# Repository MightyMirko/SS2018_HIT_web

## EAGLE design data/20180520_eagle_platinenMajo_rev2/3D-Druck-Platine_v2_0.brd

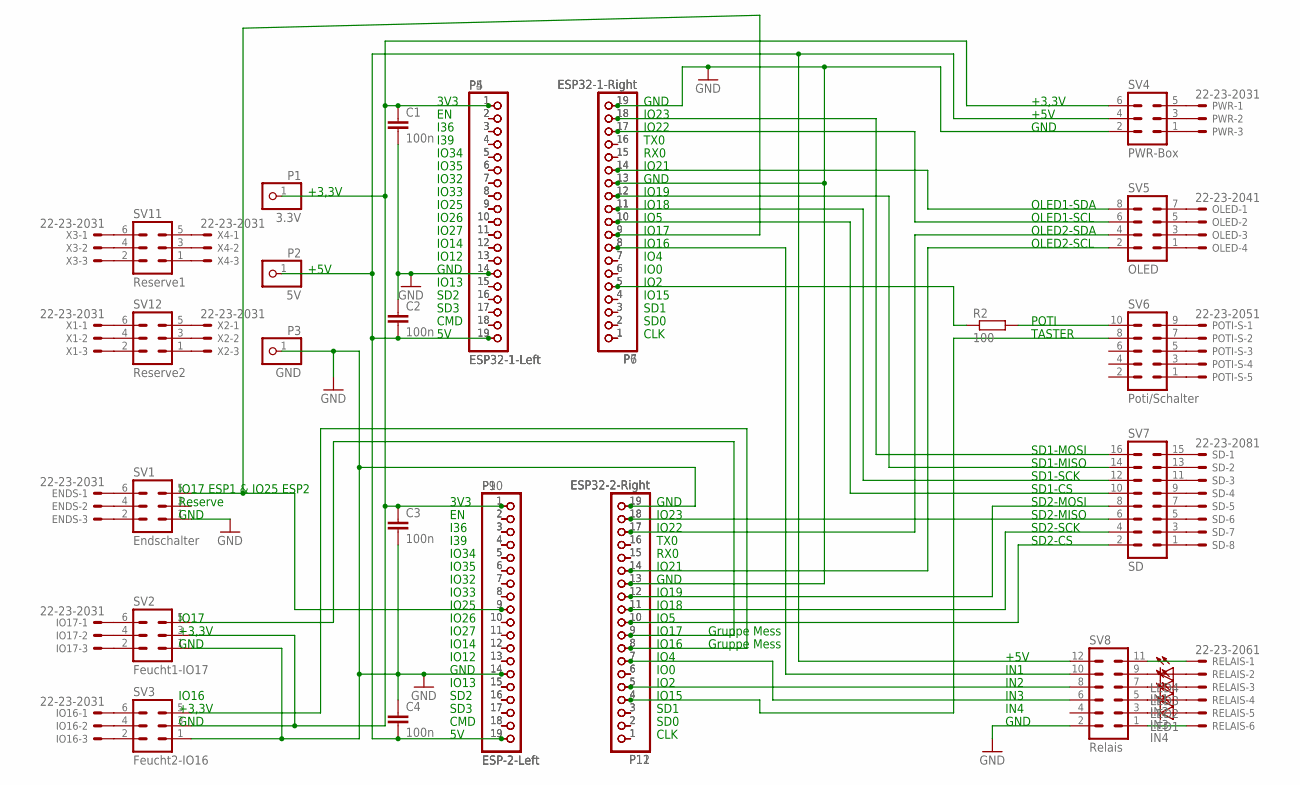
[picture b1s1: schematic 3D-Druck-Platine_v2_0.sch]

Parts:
C1, C2, C3, C4: 100n; C025-024X044
ENDS: 22-23-2031
IO16, IO17: 22-23-2031
LED1: IN4; LED3MM
LED2: IN3; LED3MM
LED3: IN2; LED3MM
LED4: IN1; LED3MM
OLED: 22-23-2041
P1: 3.3V; 1X01
P2: 5V; 1X01
P3: GND; 1X01
P4, P5: ESP32-1-Left; 1X19
P6, P7: ESP32-1-Right; 1X19
P9, P10: ESP-2-Left; 1X19
P11, P12: ESP32-2-Right; 1X19
POTI-S: 22-23-2051
PWR: 22-23-2031
R2: 100; 0207/10
RELAIS: 22-23-2061
SD: 22-23-2081
SV1: Endschalter; MA03-2
SV2: Feucht1-IO17; MA03-2
SV3: Feucht2-IO16; MA03-2
SV4: PWR-Box; MA03-2
SV5: OLED; MA04-2
SV6: Poti/Schalter; MA05-2
SV7: SD; MA08-2
SV8: Relais; MA06-2
SV11: Reserve1; MA03-2
SV12: Reserve2; MA03-2
X1, X2, X3, X4: 22-23-2031

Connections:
GND: C1.2, C2.1, C3.2, C4.1, P3.1, P4.14, P5.14, P6.13, P6.19, P7.13, P7.19, P9.14, P10.14, P11.13, P11.19, P12.13, P12.19, SV1.1, SV2.1, SV3.1, SV4.2, SV8.2
unnamed: P4.2, P5.2
unnamed: LED4.K (C), SV8.9
unnamed: P4.3, P5.3
unnamed: C1.1, C3.1, P1.1, P4.1, P5.1, P9.1, P10.1, SV2.3, SV3.3, SV4.6
unnamed: P11.8, P12.8, SV3.5
unnamed: LED3.K (C), SV8.7
unnamed: C2.2, C4.2, P2.1, P4.19, P5.19, P9.19, P10.19, SV4.4, SV8.12
unnamed: P4.4, P5.4
unnamed: P4.5, P5.5
unnamed: ENDS.1, SV1.6
unnamed: P4.6, P5.6
unnamed: IO17.1, SV2.6
unnamed: ENDS.2, SV1.4
unnamed: ENDS.3, SV1.2
unnamed: IO17.2, SV2.4
unnamed: IO17.3, SV2.2
unnamed: IO16.1, SV3.6
unnamed: IO16.2, SV3.4
unnamed: IO16.3, SV3.2
unnamed: PWR.1, SV4.5
unnamed: PWR.2, SV4.3
unnamed: LED2.K (C), SV8.5
unnamed: P4.7, P5.7
unnamed: P4.8, P5.8
unnamed: P4.9, P5.9
unnamed: P4.10, P5.10
unnamed: P4.11, P5.11
unnamed: P4.12, P5.12
unnamed: P4.13, P5.13
unnamed: P4.15, P5.15
unnamed: P4.16, P5.16
unnamed: P4.17, P5.17
unnamed: P4.18, P5.18
unnamed: P6.1, P7.1
unnamed: P6.2, P7.2
unnamed: P6.3, P7.3
unnamed: P6.4, P7.4
unnamed: PWR.3, SV4.1
unnamed: P6.7, P7.7
unnamed: P6.15, P7.15
unnamed: P6.16, P7.16
unnamed: P9.2, P10.2
unnamed: P9.3, P10.3
unnamed: P9.4, P10.4
unnamed: P9.5, P10.5
unnamed: P9.6, P10.6
unnamed: P9.8, P10.8
unnamed: P9.11, P10.11
unnamed: P9.12, P10.12
unnamed: P9.13, P10.13
unnamed: P9.15, P10.15
unnamed: P9.16, P10.16
unnamed: P9.17, P10.17
unnamed: P9.18, P10.18
unnamed: P11.1, P12.1
unnamed: P11.2, P12.2
unnamed: P11.3, P12.3
unnamed: OLED.1, SV5.7
unnamed: P11.6, P12.6
unnamed: P11.15, P12.15
unnamed: R2.2, SV6.10
unnamed: P6.6, P7.6
unnamed: OLED.2, SV5.5
unnamed: OLED.3, SV5.3
unnamed: OLED.4, SV5.1
unnamed: POTI-S.1, SV6.9
unnamed: POTI-S.2, SV6.7
unnamed: POTI-S.3, SV6.5
unnamed: POTI-S.4, SV6.3
unnamed: POTI-S.5, SV6.1
unnamed: SD.1, SV7.15
unnamed: SD.2, SV7.13
unnamed: SD.3, SV7.11
unnamed: SD.5, SV7.7
unnamed: SD.6, SV7.5
unnamed: SD.7, SV7.3
unnamed: SD.8, SV7.1
unnamed: SD.4, SV7.9
unnamed: RELAIS.1, SV8.11
unnamed: LED1.K (C), SV8.3
unnamed: LED4.A, RELAIS.2
unnamed: LED3.A, RELAIS.3
unnamed: LED2.A, RELAIS.4
unnamed: RELAIS.6, SV8.1
unnamed: LED1.A, RELAIS.5
unnamed: SV11.6, X3.1
unnamed: SV11.4, X3.2
unnamed: SV11.2, X3.3
unnamed: SV11.5, X4.1
unnamed: SV11.3, X4.2
unnamed: SV11.1, X4.3
unnamed: SV12.6, X1.1
unnamed: SV12.4, X1.2
unnamed: SV12.2, X1.3
unnamed: SV12.5, X2.1
unnamed: SV12.3, X2.2
unnamed: SV12.1, X2.3
unnamed: P11.16, P12.16
N$ESP1-18: P6.11, P7.11, SV7.12
N$ESP1-IO2: P6.5, P7.5, R2.1
N$ESP1-IO5: P6.10, P7.10, SV7.10
N$ESP1-IO16: P6.8, P7.8, SV8.10
N$ESP1-IO17_ESP2-IO25: P6.9, P7.9, P9.9, P10.9, SV1.5
N$ESP1-IO19: P6.12, P7.12, SV7.14
N$ESP1-IO21: P6.14, P7.14, SV5.8
N$ESP1-IO22: P6.17, P7.17, SV5.6
N$ESP1-IO23: P6.18, P7.18, SV7.16
N$ESP2-IO2: P11.5, P12.5, SV8.8
N$ESP2-IO4: P11.7, P12.7, SV8.6
N$ESP2-IO5: P11.10, P12.10, SV7.2
N$ESP2-IO15: P11.4, P12.4, SV6.8
N$ESP2-IO16: P11.9, P12.9, SV2.5
N$ESP2-IO18: P11.11, P12.11, SV7.4
N$ESP2-IO19: P11.12, P12.12, SV7.8
N$ESP2-IO21: P11.14, P12.14, SV5.2
N$ESP2-IO22: P11.17, P12.17, SV5.4
N$ESP2-IO23: P11.18, P12.18, SV7.6
N$ESP2-IO26: P9.10, P10.10
N$ESP2-IO32: P9.7, P10.7

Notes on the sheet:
3V3
I36
I39
IO34
IO35
IO32
IO33
IO25
IO26
IO27
IO14
IO12
GND
IO13
SD2
SD3
CMD
IO23
IO22
TX0
RX0
IO21
IO18
IO19
IO5
IO17
IO16
IO4
IO0
IO2
IO15
SD1
SD0
CLK
+5V
+3,3V
OLED1-SDA
OLED2-SDA
OLED2-SCL
OLED1-SCL

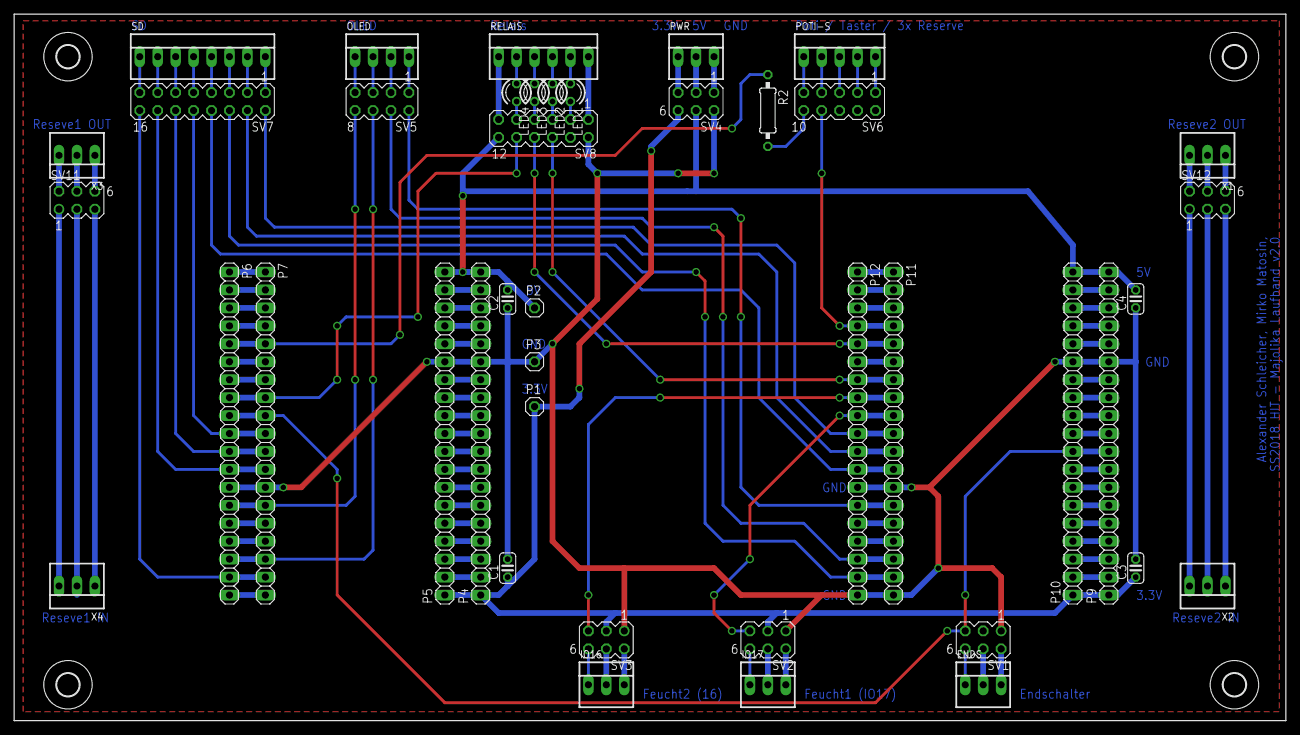
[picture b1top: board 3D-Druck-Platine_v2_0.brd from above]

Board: 2 copper layers, 180.0 x 100.0 mm, 46 parts (0 on the bottom side), 120 nets.

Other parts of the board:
U$1, U$2, U$3, U$4: 3,2

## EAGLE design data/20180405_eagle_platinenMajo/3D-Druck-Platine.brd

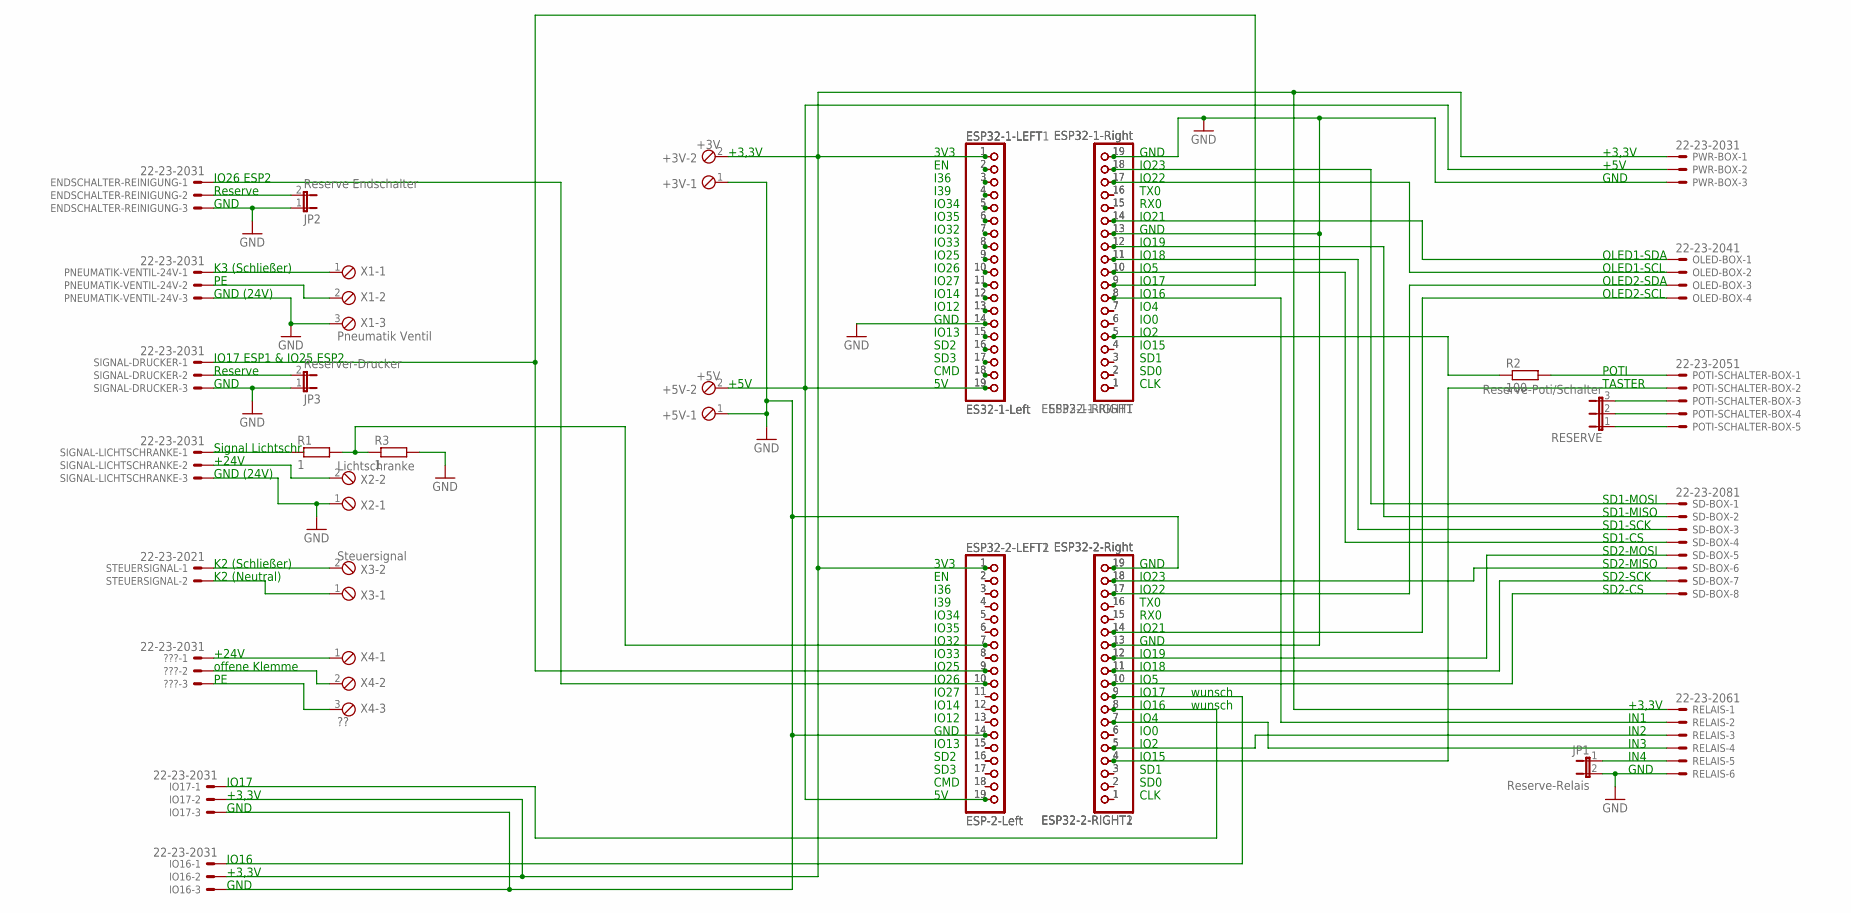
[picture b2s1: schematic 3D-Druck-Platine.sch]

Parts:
+3V: +3V; 2POL254
+5V: +5V; 2POL254
???: 22-23-2031
ENDSCHALTER-REINIGUNG: 22-23-2031
ESP32-1-LEFT, ESP32-1-LEFT1: ES32-1-Left; 1X19
ESP32-1-RIGHT, ESP32-1-RIGHT1: ESP32-1-Right; 1X19
ESP32-2-LEFT1, ESP32-2-LEFT2: ESP-2-Left; 1X19
ESP32-2-RIGHT1, ESP32-2-RIGHT2: ESP32-2-Right; 1X19
IO16, IO17: 22-23-2031
JP1: Reserve-Relais; JP1
JP2: Reserve Endschalter; JP1
JP3: Reserver-Drucker; JP1
OLED-BOX: 22-23-2041
PNEUMATIK-VENTIL-24V: 22-23-2031
POTI-SCHALTER-BOX: 22-23-2051
PWR-BOX: 22-23-2031
R1, R3: 1; 0207/10
R2: 100; 0207/10
RELAIS: 22-23-2061
RESERVE: Reserve-Poti/Schalter; JP2
SD-BOX: 22-23-2081
SIGNAL-DRUCKER: 22-23-2031
SIGNAL-LICHTSCHRANKE: 22-23-2031
STEUERSIGNAL: 22-23-2021
X1: Pneumatik Ventil; 3POL254
X2: Lichtschranke; 2POL254
X3: Steuersignal; 2POL254
X4: ??; 3POL254

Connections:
GND: +3V.1, +5V.1, ENDSCHALTER-REINIGUNG.3, ESP32-1-LEFT.14, ESP32-1-LEFT1.14, ESP32-1-RIGHT.13, ESP32-1-RIGHT.19, ESP32-1-RIGHT1.13, ESP32-1-RIGHT1.19, ESP32-2-LEFT1.14, ESP32-2-LEFT2.14, ESP32-2-RIGHT1.13, ESP32-2-RIGHT1.19, ESP32-2-RIGHT2.13, ESP32-2-RIGHT2.19, IO16.3, IO17.3, JP1.2, JP2.1, JP3.1, PNEUMATIK-VENTIL-24V.3, PWR-BOX.3, R3.2, RELAIS.6, SIGNAL-DRUCKER.3, SIGNAL-LICHTSCHRANKE.3, X1.3, X2.1
unnamed: ESP32-1-LEFT.2, ESP32-1-LEFT1.2
unnamed: POTI-SCHALTER-BOX.3, RESERVE.3
unnamed: ESP32-1-LEFT.3, ESP32-1-LEFT1.3
unnamed: +3V.2, ESP32-1-LEFT.1, ESP32-1-LEFT1.1, ESP32-2-LEFT1.1, ESP32-2-LEFT2.1, IO16.2, IO17.2, PWR-BOX.1, RELAIS.1
unnamed: POTI-SCHALTER-BOX.4, RESERVE.2
unnamed: POTI-SCHALTER-BOX.5, RESERVE.1
unnamed: +5V.2, ESP32-1-LEFT.19, ESP32-1-LEFT1.19, ESP32-2-LEFT1.19, ESP32-2-LEFT2.19, PWR-BOX.2
unnamed: ESP32-1-LEFT.4, ESP32-1-LEFT1.4
unnamed: ESP32-1-LEFT.5, ESP32-1-LEFT1.5
unnamed: ENDSCHALTER-REINIGUNG.2, JP2.2
unnamed: ESP32-1-LEFT.6, ESP32-1-LEFT1.6
unnamed: JP3.2, SIGNAL-DRUCKER.2
unnamed: R1.1, SIGNAL-LICHTSCHRANKE.1
unnamed: SIGNAL-LICHTSCHRANKE.2, X2.2
unnamed: PNEUMATIK-VENTIL-24V.1, X1.1
unnamed: STEUERSIGNAL.1, X3.2
unnamed: STEUERSIGNAL.2, X3.1
unnamed: PNEUMATIK-VENTIL-24V.2, X1.2
unnamed: ???.1, X4.1
unnamed: ???.2, X4.2
unnamed: ???.3, X4.3
unnamed: JP1.1, RELAIS.5
unnamed: ESP32-1-LEFT.7, ESP32-1-LEFT1.7
unnamed: ESP32-1-LEFT.8, ESP32-1-LEFT1.8
unnamed: ESP32-1-LEFT.9, ESP32-1-LEFT1.9
unnamed: ESP32-1-LEFT.10, ESP32-1-LEFT1.10
unnamed: ESP32-1-LEFT.11, ESP32-1-LEFT1.11
unnamed: ESP32-1-LEFT.12, ESP32-1-LEFT1.12
unnamed: ESP32-1-LEFT.13, ESP32-1-LEFT1.13
unnamed: ESP32-1-LEFT.15, ESP32-1-LEFT1.15
unnamed: ESP32-1-LEFT.16, ESP32-1-LEFT1.16
unnamed: ESP32-1-LEFT.17, ESP32-1-LEFT1.17
unnamed: ESP32-1-LEFT.18, ESP32-1-LEFT1.18
unnamed: ESP32-1-RIGHT.1, ESP32-1-RIGHT1.1
unnamed: ESP32-1-RIGHT.2, ESP32-1-RIGHT1.2
unnamed: ESP32-1-RIGHT.3, ESP32-1-RIGHT1.3
unnamed: ESP32-1-RIGHT.4, ESP32-1-RIGHT1.4
unnamed: ESP32-1-RIGHT.7, ESP32-1-RIGHT1.7
unnamed: ESP32-1-RIGHT.15, ESP32-1-RIGHT1.15
unnamed: ESP32-1-RIGHT.16, ESP32-1-RIGHT1.16
unnamed: ESP32-2-LEFT1.2, ESP32-2-LEFT2.2
unnamed: ESP32-2-LEFT1.3, ESP32-2-LEFT2.3
unnamed: ESP32-2-LEFT1.4, ESP32-2-LEFT2.4
unnamed: ESP32-2-LEFT1.5, ESP32-2-LEFT2.5
unnamed: ESP32-2-LEFT1.6, ESP32-2-LEFT2.6
unnamed: ESP32-2-LEFT1.8, ESP32-2-LEFT2.8
unnamed: ESP32-2-LEFT1.11, ESP32-2-LEFT2.11
unnamed: ESP32-2-LEFT1.12, ESP32-2-LEFT2.12
unnamed: ESP32-2-LEFT1.13, ESP32-2-LEFT2.13
unnamed: ESP32-2-LEFT1.15, ESP32-2-LEFT2.15
unnamed: ESP32-2-LEFT1.16, ESP32-2-LEFT2.16
unnamed: ESP32-2-LEFT1.17, ESP32-2-LEFT2.17
unnamed: ESP32-2-LEFT1.18, ESP32-2-LEFT2.18
unnamed: ESP32-2-RIGHT1.1, ESP32-2-RIGHT2.1
unnamed: ESP32-2-RIGHT1.2, ESP32-2-RIGHT2.2
unnamed: ESP32-2-RIGHT1.3, ESP32-2-RIGHT2.3
unnamed: ESP32-2-RIGHT1.6, ESP32-2-RIGHT2.6
unnamed: ESP32-2-RIGHT1.15, ESP32-2-RIGHT2.15
unnamed: POTI-SCHALTER-BOX.1, R2.2
unnamed: ESP32-1-RIGHT.6, ESP32-1-RIGHT1.6
unnamed: ESP32-2-RIGHT1.16, ESP32-2-RIGHT2.16
N$ESP1-18: ESP32-1-RIGHT.11, ESP32-1-RIGHT1.11, SD-BOX.3
N$ESP1-IO2: ESP32-1-RIGHT.5, ESP32-1-RIGHT1.5, R2.1
N$ESP1-IO5: ESP32-1-RIGHT.10, ESP32-1-RIGHT1.10, SD-BOX.4
N$ESP1-IO16: ESP32-1-RIGHT.8, ESP32-1-RIGHT1.8, RELAIS.2
N$ESP1-IO17_ESP2-IO25: ESP32-1-RIGHT.9, ESP32-1-RIGHT1.9, ESP32-2-LEFT1.9, ESP32-2-LEFT2.9, SIGNAL-DRUCKER.1
N$ESP1-IO19: ESP32-1-RIGHT.12, ESP32-1-RIGHT1.12, SD-BOX.2
N$ESP1-IO21: ESP32-1-RIGHT.14, ESP32-1-RIGHT1.14, OLED-BOX.1
N$ESP1-IO22: ESP32-1-RIGHT.17, ESP32-1-RIGHT1.17, OLED-BOX.2
N$ESP1-IO23: ESP32-1-RIGHT.18, ESP32-1-RIGHT1.18, SD-BOX.1
N$ESP2-IO2: ESP32-2-RIGHT1.5, ESP32-2-RIGHT2.5, RELAIS.3
N$ESP2-IO4: ESP32-2-RIGHT1.7, ESP32-2-RIGHT2.7, RELAIS.4
N$ESP2-IO5: ESP32-2-RIGHT1.10, ESP32-2-RIGHT2.10, SD-BOX.8
N$ESP2-IO15: ESP32-2-RIGHT1.4, ESP32-2-RIGHT2.4, POTI-SCHALTER-BOX.2
N$ESP2-IO16: ESP32-2-RIGHT1.8, ESP32-2-RIGHT2.8, IO17.1
N$ESP2-IO17: ESP32-2-RIGHT1.9, ESP32-2-RIGHT2.9, IO16.1
N$ESP2-IO18: ESP32-2-RIGHT1.11, ESP32-2-RIGHT2.11, SD-BOX.7
N$ESP2-IO19: ESP32-2-RIGHT1.12, ESP32-2-RIGHT2.12, SD-BOX.5
N$ESP2-IO21: ESP32-2-RIGHT1.14, ESP32-2-RIGHT2.14, OLED-BOX.4
N$ESP2-IO22: ESP32-2-RIGHT1.17, ESP32-2-RIGHT2.17, OLED-BOX.3
N$ESP2-IO23: ESP32-2-RIGHT1.18, ESP32-2-RIGHT2.18, SD-BOX.6
N$ESP2-IO26: ENDSCHALTER-REINIGUNG.1, ESP32-2-LEFT1.10, ESP32-2-LEFT2.10
N$ESP2-IO32: ESP32-2-LEFT1.7, ESP32-2-LEFT2.7, R1.2, R3.1

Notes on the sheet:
3V3
I36
I39
IO34
IO35
IO32
IO33
IO25
IO26
IO27
IO14
IO12
GND
IO13
SD2
SD3
CMD
IO23
IO22
TX0
RX0
IO21
IO18
IO19
IO5
IO17
IO16
IO4
IO0
IO2
IO15
SD1
SD0
CLK
+5V
+3,3V
OLED1-SDA
OLED2-SDA
OLED2-SCL
OLED1-SCL

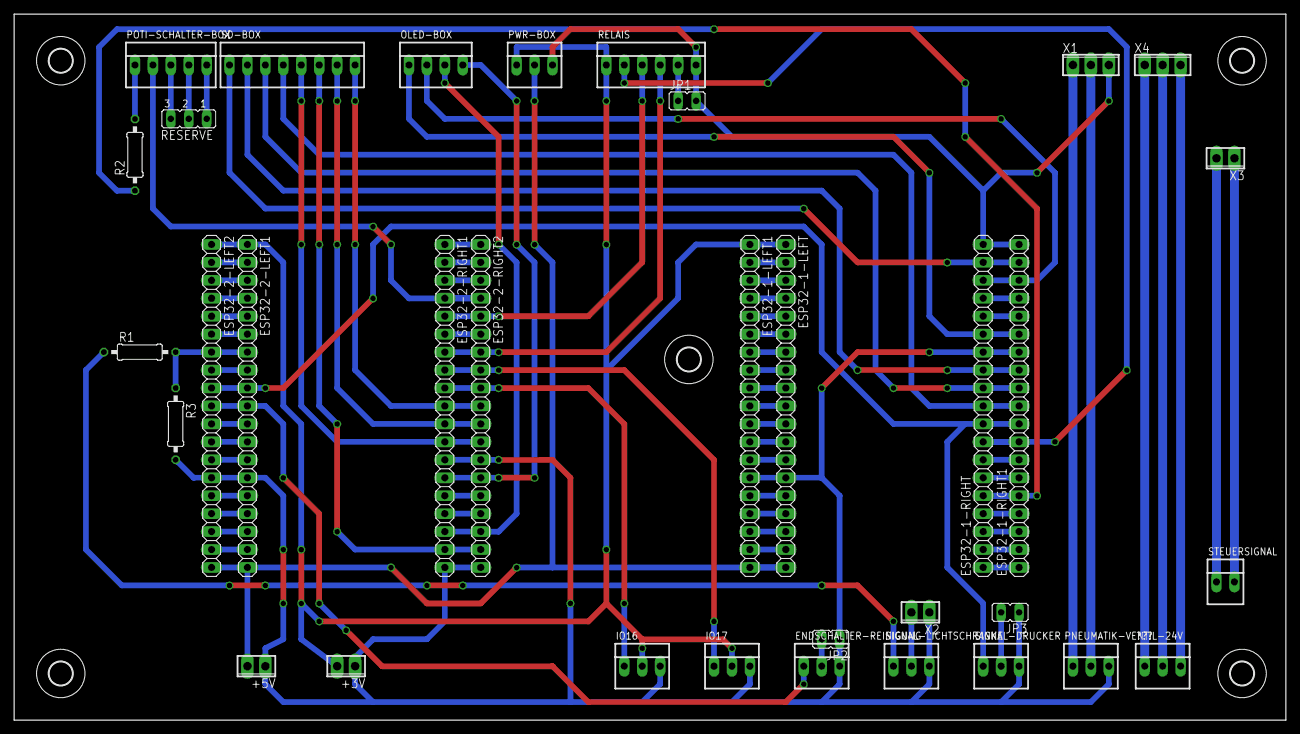
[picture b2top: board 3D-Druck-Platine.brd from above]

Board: 1 copper layer, 180.0 x 99.9 mm, 39 parts (0 on the bottom side), 84 nets.

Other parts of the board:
U$1, U$2, U$3, U$4, U$5: 3,3

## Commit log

2018-04-05 layout und eagle zip hinzefügt. Stand der TEchnik verbessert und die calc sheets umbenannt und eingebettet.
2018-04-05 Portbelegungsplan hinzugefügt
2018-04-10 BoM Download hinzugefügt. EagleZip gefixt.
2018-04-10 Bis Stand der Technik - Punkt Quelle, yt Größe, bild fehlt,
2018-04-18 Anleitung und Protokolle gepatcht. Stand der Technik vom letzten Commit steht noch aus Vorlage.dwt wurde auf utf-8 geändert. Dadurch kann man nun Umlaute nutzen.
2018-04-18 weiter im TODO. Links repariert
2018-04-18 Design.css und portbelegungsplan geändert per Hand
2018-04-18 Portbelegungsplan erfolgreich angepasst. Navigationsstrukturen wurden automatisch von Expression Web4 gemerget - #TODO Checke di eNav Struktur
2018-04-18 Verschiedene Pages weitergeführt
2018-04-18 removed fucking vti
2018-04-18 Aufrauemen unbenötigter Dateien - default.css?
2018-04-18 Betastatus erreicht. Vorlage.dwt geändert - jetzt ist es breiter. Dies ist für die Vorlesungen besser
2018-04-18 präsentable Version
2018-04-18 Hallo GitHub - habe das repo ins Hub abgelegt. Den Link habe ich in die 0412Linkliste.html abgelegt.
2018-04-19 Bedienungsanleitung Fehler Verbessert
2018-04-19 Noch paar kleinigkeiten angepasst
2018-04-19 portbelegungsplan angepasst und tabelle verschönert (rahmen)
2018-04-19 Seltsamer Fehler. In der Ausarbeitung fehlt manchmal ein Listeneintrag im DropDownMenu
2018-05-02 angepasst nach Praesi
2018-05-02 Bilder extrahiert
2018-05-02 0401 0411 upgedated.. Platinenbild ist online.. Momentane Lösung haben wir leider kein Bild von
2018-05-02 quellcode hizugefuegt
2018-05-20 Anpassen auf version2.0- Ausgewaehlte Loesungen und Bilder wurden hochgeladen
